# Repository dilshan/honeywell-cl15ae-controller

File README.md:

# Replacement driver for Honeywell CL15AE

PIC16F819 based replacement driver unit for Honeywell (JMTEK) CL15AE evaporative air cooler.

Detail posting about this project is available at [jayakody2000lk.blogspot.com](http://jayakody2000lk.blogspot.com/2019/07/replacement-driver-for-honeywell-cl15ae.html).

**WARNING:** This unit has a direct connection with the AC mains voltage and makes sure to take all necessary precautions while assembling, testing and installing this board. Improper connection or short-circuits would cause lethal shock or fire!

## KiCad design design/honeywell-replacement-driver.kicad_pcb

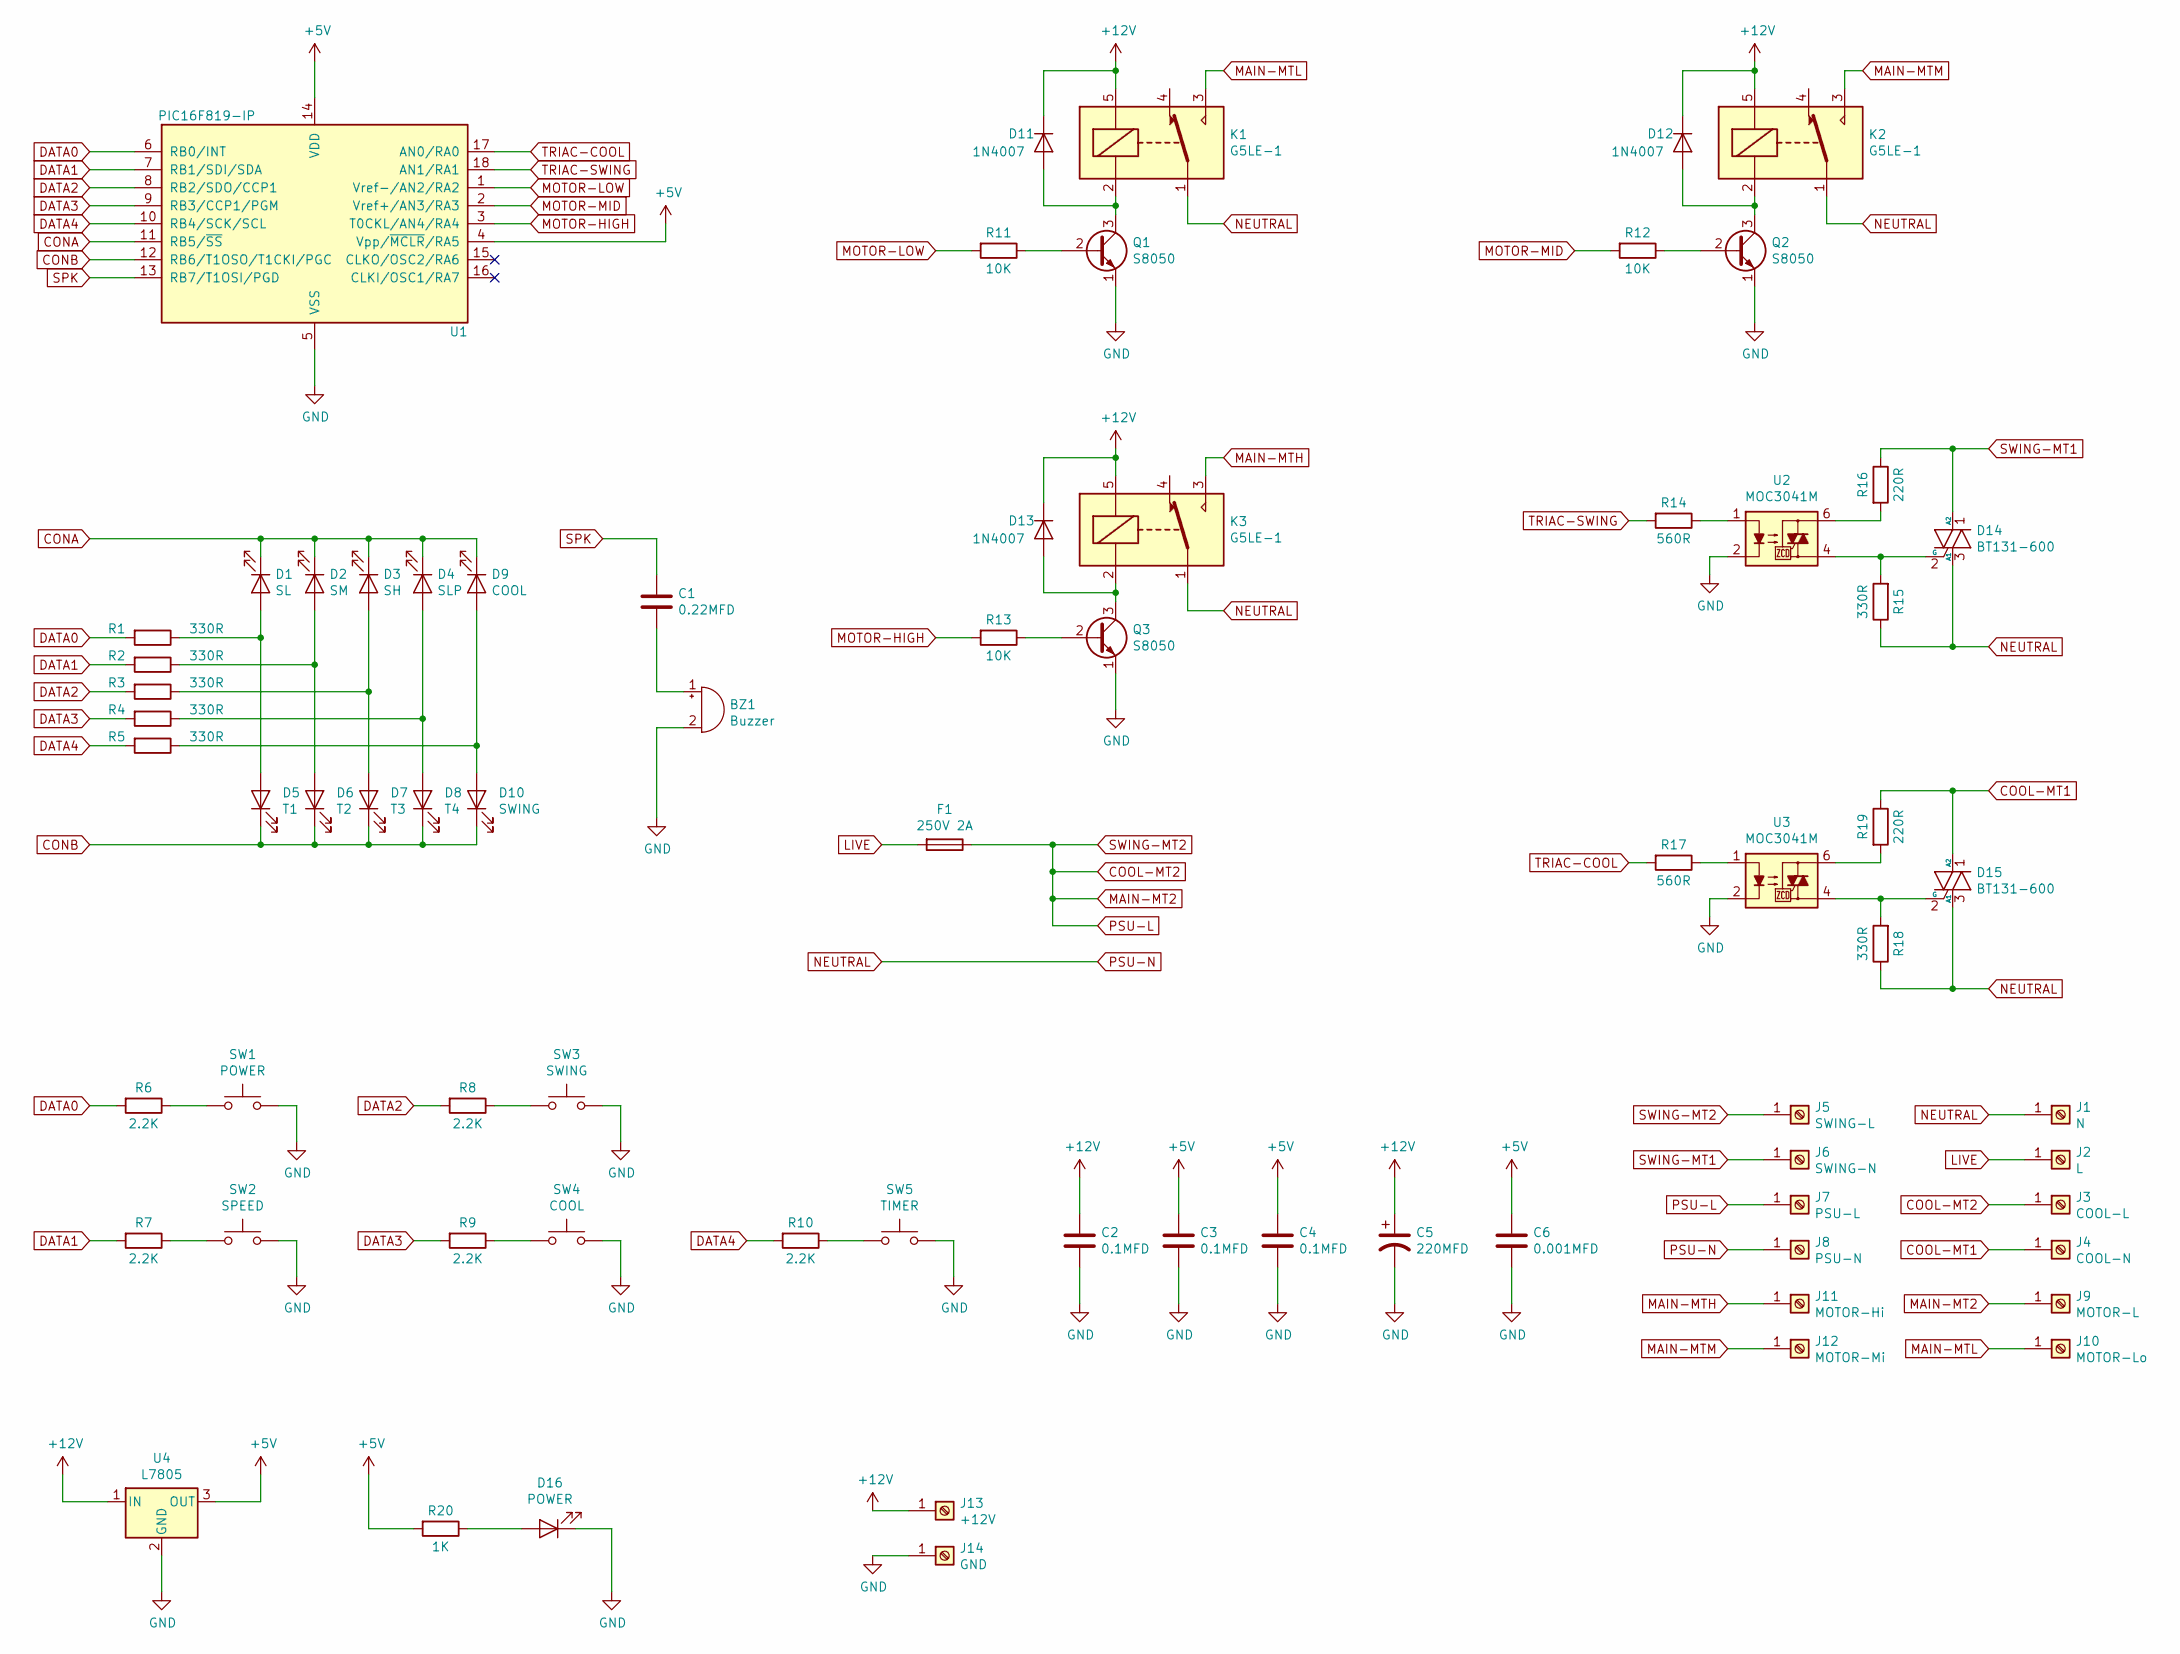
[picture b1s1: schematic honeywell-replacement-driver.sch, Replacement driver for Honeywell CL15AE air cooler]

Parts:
BZ1: Buzzer; Buzzer_12x9.5RM7.6
C1: 0.22MFD; C_Disc_D9.0mm_W5.0mm_P7.50mm
C2, C3, C4: 0.1MFD; C_Disc_D9.0mm_W5.0mm_P7.50mm
C5: 220MFD; CP_Radial_D8.0mm_P3.80mm
C6: 0.001MFD; C_Disc_D4.7mm_W2.5mm_P5.00mm
D1: SL; LED_D5.0mm
D2: SM; LED_D5.0mm
D3: SH; LED_D5.0mm
D4: SLP; LED_D5.0mm
D5: T1; LED_D5.0mm
D6: T2; LED_D5.0mm
D7: T3; LED_D5.0mm
D8: T4; LED_D5.0mm
D9: COOL; LED_D5.0mm
D10: SWING; LED_D5.0mm
D11, D12, D13: 1N4007; D_DO-41_SOD81_P10.16mm_Horizontal
D14, D15: BT131-600; TO-92_HandSolder
D16: POWER; LED_D5.0mm
F1: 250V 2A; L_Axial_L5.3mm_D2.2mm_P10.16mm_Horizontal_Vishay_IM-1
J1: N; TestPoint_Loop_D2.60mm_Drill1.6mm_Beaded
J2: L; TestPoint_Loop_D2.60mm_Drill1.6mm_Beaded
J3: COOL-L; TestPoint_Loop_D2.60mm_Drill1.6mm_Beaded
J4: COOL-N; TestPoint_Loop_D2.60mm_Drill1.6mm_Beaded
J5: SWING-L; TestPoint_Loop_D2.60mm_Drill1.6mm_Beaded
J6: SWING-N; TestPoint_Loop_D2.60mm_Drill1.6mm_Beaded
J7: PSU-L; TestPoint_Loop_D2.60mm_Drill1.6mm_Beaded
J8: PSU-N; TestPoint_Loop_D2.60mm_Drill1.6mm_Beaded
J9: MOTOR-L; TestPoint_Loop_D2.60mm_Drill1.6mm_Beaded
J10: MOTOR-Lo; TestPoint_Loop_D2.60mm_Drill1.6mm_Beaded
J11: MOTOR-Hi; TestPoint_Loop_D2.60mm_Drill1.6mm_Beaded
J12: MOTOR-Mi; TestPoint_Loop_D2.60mm_Drill1.6mm_Beaded
J13: +12V; TestPoint_Loop_D2.60mm_Drill1.6mm_Beaded
J14: GND; TestPoint_Loop_D2.60mm_Drill1.6mm_Beaded
K1, K2, K3: G5LE-1; Relay_SPDT_Omron-G5LE-1
Q1, Q2, Q3: S8050; TO-92_HandSolder
R1, R2, R3, R4, R5, R15, R18: 330R; R_Axial_DIN0207_L6.3mm_D2.5mm_P10.16mm_Horizontal
R6, R7, R8, R9, R10: 2.2K; R_Axial_DIN0207_L6.3mm_D2.5mm_P10.16mm_Horizontal
R11, R12, R13: 10K; R_Axial_DIN0207_L6.3mm_D2.5mm_P10.16mm_Horizontal
R14, R17: 560R; R_Axial_DIN0207_L6.3mm_D2.5mm_P10.16mm_Horizontal
R16, R19: 220R; R_Axial_DIN0207_L6.3mm_D2.5mm_P10.16mm_Horizontal
R20: 1K; R_Axial_DIN0207_L6.3mm_D2.5mm_P10.16mm_Horizontal
SW1: POWER; SW_PUSH_6mm
SW2: SPEED; SW_PUSH_6mm
SW3: SWING; SW_PUSH_6mm
SW4: COOL; SW_PUSH_6mm
SW5: TIMER; SW_PUSH_6mm
U1: PIC16F819-IP; DIP-18_W7.62mm_Socket_LongPads
U2, U3: MOC3041M; DIP-6_W7.62mm_LongPads
U4: L7805; TO-220-3_Horizontal_TabDown

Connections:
+5V: C3.1, C4.1, C6.1, R20.2, U1.4 (Vpp/~MCLR~/RA5), U1.14 (VDD), U4.3 (OUT)
+12V: C2.1, C5.1, D11.1 (K), D12.1 (K), D13.1 (K), J13.1, K1.5, K2.5, K3.5, U4.1 (IN)
CONA: D1.1 (K), D2.1 (K), D3.1 (K), D4.1 (K), D9.1 (K), U1.11 (RB5/~SS~)
CONB: D5.1 (K), D6.1 (K), D7.1 (K), D8.1 (K), D10.1 (K), U1.12 (RB6/T1OSO/T1CKI/PGC)
COOL-MT1: D15.1 (A2), J4.1, R19.1
COOL-MT2: F1.1, J3.1, J5.1, J7.1, J9.1
DATA0: R1.2, R6.2, U1.6 (RB0/INT)
DATA1: R2.2, R7.2, U1.7 (RB1/SDI/SDA)
DATA2: R3.2, R8.2, U1.8 (RB2/SDO/CCP1)
DATA3: R4.2, R9.2, U1.9 (RB3/CCP1/PGM)
DATA4: R5.2, R10.2, U1.10 (RB4/SCK/SCL)
GND: BZ1.2 (+), C2.2, C3.2, C4.2, C5.2, C6.2, D16.1 (K), J14.1, Q1.1 (E), Q2.1 (E), Q3.1 (E), SW1.2, SW2.2, SW3.2, SW4.2, SW5.2, U1.5 (VSS), U2.2, U3.2, U4.2 (GND)
LIVE: F1.2, J2.1
MAIN-MTH: J11.1, K3.3
MAIN-MTL: J10.1, K1.3
MAIN-MTM: J12.1, K2.3
MOTOR-HIGH: R13.2, U1.3 (T0CKL/AN4/RA4)
MOTOR-LOW: R11.2, U1.1 (Vref-/AN2/RA2)
MOTOR-MID: R12.2, U1.2 (Vref+/AN3/RA3)
NEUTRAL: D14.3 (A1), D15.3 (A1), J1.1, J8.1, K1.1, K2.1, K3.1, R15.1, R18.1
unnamed: BZ1.1 (-), C1.2
unnamed: D1.2 (A), D5.2 (A), R1.1
unnamed: D2.2 (A), D6.2 (A), R2.1
unnamed: D3.2 (A), D7.2 (A), R3.1
unnamed: D4.2 (A), D8.2 (A), R4.1
unnamed: D9.2 (A), D10.2 (A), R5.1
unnamed: D11.2 (A), K1.2, Q1.3 (C)
unnamed: D12.2 (A), K2.2, Q2.3 (C)
unnamed: D13.2 (A), K3.2, Q3.3 (C)
unnamed: D14.2 (G), R15.2, U2.4
unnamed: D15.2 (G), R18.2, U3.4
unnamed: D16.2 (A), R20.1
unnamed: Q1.2 (B), R11.1
unnamed: Q2.2 (B), R12.1
unnamed: Q3.2 (B), R13.1
unnamed: R6.1, SW1.1
unnamed: R7.1, SW2.1
unnamed: R8.1, SW3.1
unnamed: R9.1, SW4.1
unnamed: R10.1, SW5.1
unnamed: R14.1, U2.1
unnamed: R16.2, U2.6
unnamed: R17.1, U3.1
unnamed: R19.2, U3.6
SPK: C1.1, U1.13 (RB7/T1OSI/PGD)
SWING-MT1: D14.1 (A2), J6.1, R16.1
TRIAC-COOL: R17.2, U1.17 (AN0/RA0)
TRIAC-SWING: R14.2, U1.18 (AN1/RA1)

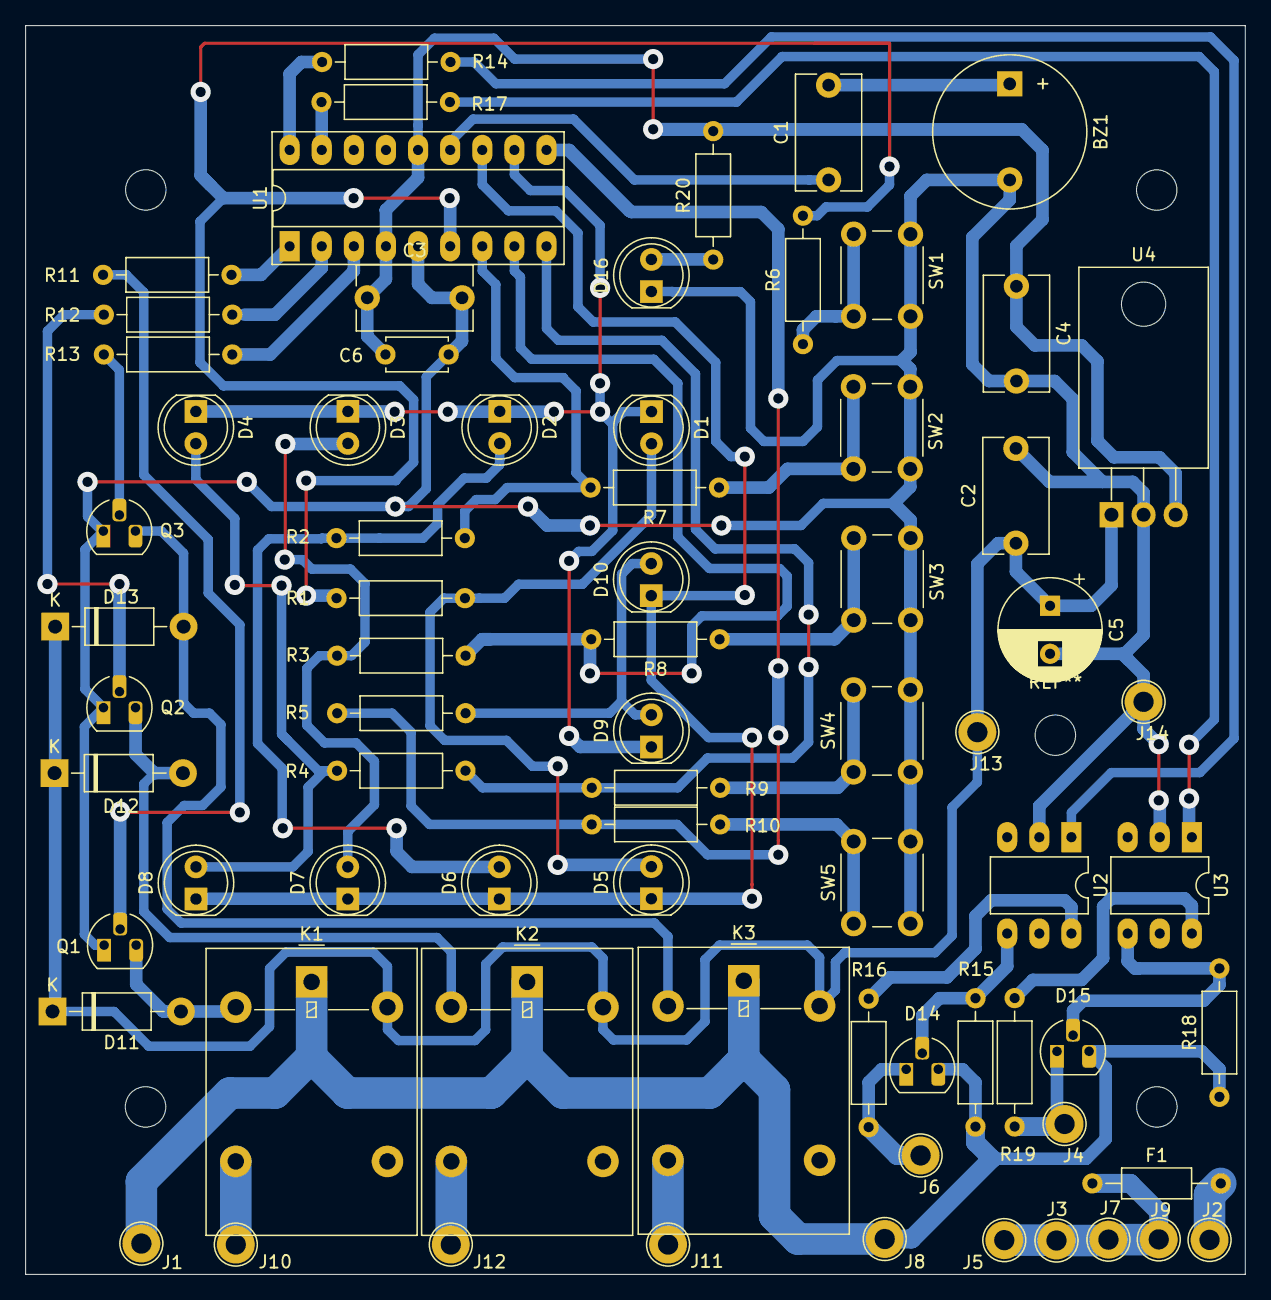
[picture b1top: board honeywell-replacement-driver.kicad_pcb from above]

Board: 2 copper layers, 96.5 x 98.8 mm, 77 parts (0 on the bottom side), 48 nets.

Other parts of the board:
 : MountingHole_3.2mm_M3
 #2,  #3,  #4: MountingHole_3.2mm_M3

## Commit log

2019-07-30 Initial version of the project.
2019-07-30 Update readme file with prototype board.
2019-07-30 Update readme file.
2019-07-30 Fix correction in JMATEK.
2019-07-30 Add link to blogspot posting.
